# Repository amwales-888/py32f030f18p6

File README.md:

# py32f030f18p6
Simple breakout board for py32f030f18p6

- 3.3v LDO powered from 5V USB.
- UART connectivity to USB via ch340k optionally connected using jumpers.
- ARM SWD programming interface header.
- All other pins are broken out to headers.
- 1 LED optionally connected to pin PB5 using jumper.
- 1 Button optionally connected to pin PA8 using jumper.
- 1 Button connected to RESET pin, pulled high.
- Booloader selected by putting jumper across BOOT0 and 3v3 pins

<table>
  <tr>
    <td> </td>
    <td> </td>
  </tr>
  <tr>
    <td> </td>
    <td> </td>
  </tr>
  <tr>
    <td> </td>
    <td> </td>
  </tr>
  <tr>
    <td> </td>
  </tr>
</table>

Resources

<li>https://www.puyasemi.com/en/py32_series.html</li>
<li>https://www.eevblog.com/forum/microcontrollers/$0-11-py32f002a-m0-24mhz-320kb-actually-324kb-more-peripherals/</li>
<li>https://www.cnblogs.com/milton/p/18168592</li>
<li>https://github.com/IOsetting/py32f0-template/tree/main</li>
<li>https://www.cnblogs.com/milton/p/17111286.html</li>
<li>https://www.cnblogs.com/milton/p/18168592</li>
<li>https://www.lcsc.com/product-detail/C3018715.html</li>

<BR>

Notes - Assembled board with 24Mhz crystal, flashed and tested with simple LED blink/UART code via the connected via USB. Used jlink clone connected via SWD and built with keil uvision, connected jlink to reset pin. Verified running at 48Mhz by timing blink rate of LED. Have not tested bootloader configuration yet.

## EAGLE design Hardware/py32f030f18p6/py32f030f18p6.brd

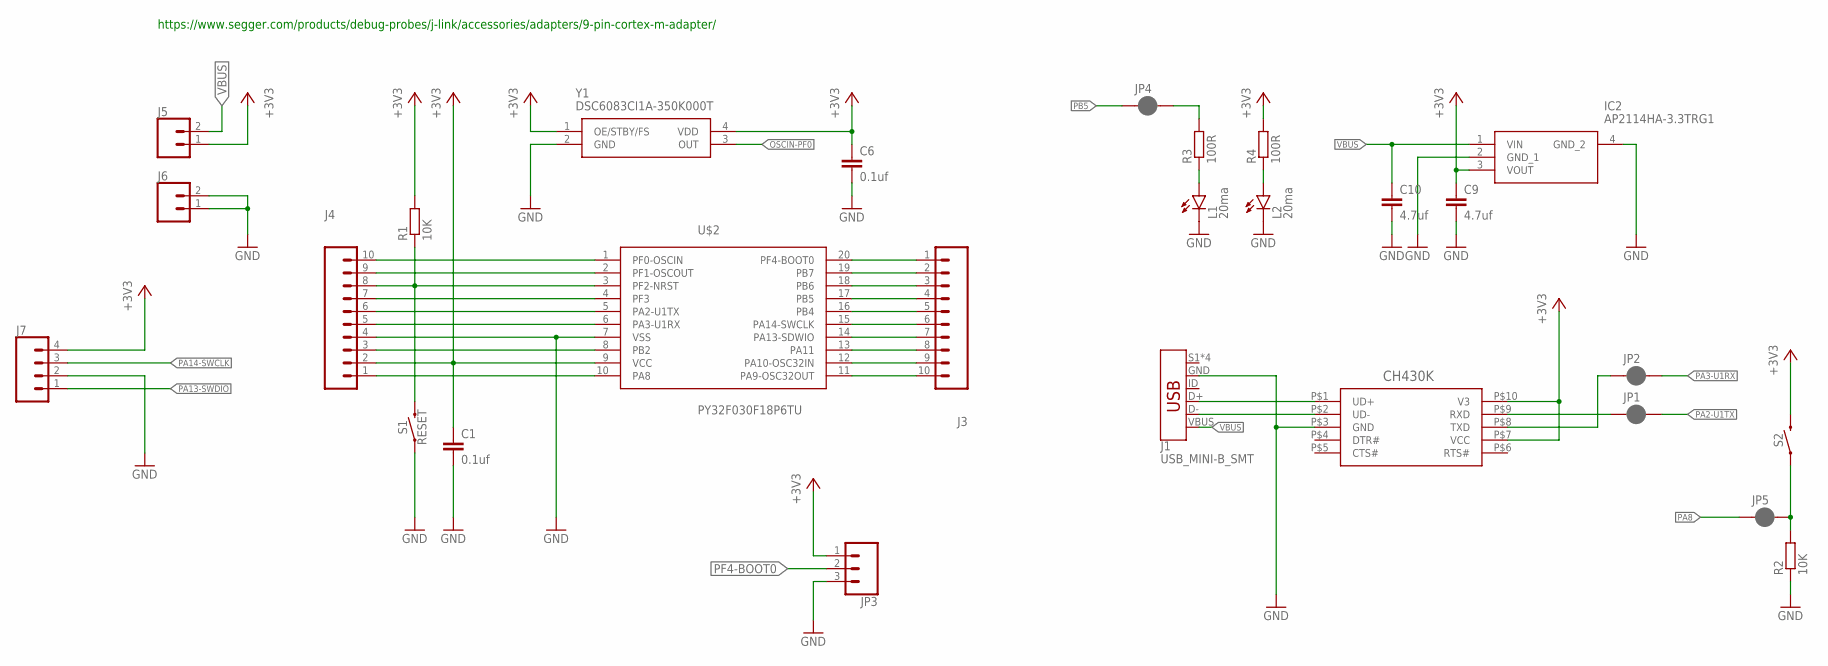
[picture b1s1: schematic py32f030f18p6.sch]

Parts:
C1, C6: 0.1uf; C0805
C9, C10: 4.7uf; C1206
IC2: AP2114HA-3.3TRG1; SOT230P700X180-4N
J1: USB_MINI-B_SMT; USB-MINIB
J3, J4: CONN_10"; 1X10
J5, J6: CONN_02; 1X02
J7: CONN_04PTH; 1X04
JP1, JP2, JP4, JP5: JUMPER-SMT_2_NC_PASTE_SILK; SMT-JUMPER_2_NC_PASTE_SILK
JP3: 455-1750-1-ND; 1X03
L1, L2: 20ma; SML0805
R1, R2: 10K; R0805
R3, R4: 100R; R0805
S1, S2: RESET; TACTILE_SWITCH_SMD_6.0X3.5MM
U$1: CH430K; ESSOP-10
U$2: PY32F030F18P6TU; TSSOP20
Y1: DSC6083CI1A-350K000T; DSC6083CI1A350K000T

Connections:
+3V3: C1.1, C6.1, C9.1, IC2.3 (VOUT), J4.2, J5.1, J7.4, JP3.1, R1.2, R4.2, S2.2, U$1.P$7 (VCC), U$1.P$10 (V3), U$2.9 (VCC), Y1.1 (OE/STBY/FS), Y1.4 (VDD)
GND: C1.2, C6.2, C9.2, C10.2, IC2.2 (GND_1), IC2.4 (GND_2), J1.GND, J4.4, J6.1, J6.2, J7.2, JP3.3, L1.C, L2.C, R2.1, S1.1, U$1.P$3 (GND), U$2.7 (VSS), Y1.2 (GND)
unnamed: L1.A, R3.1
unnamed: JP4.2, R3.2
unnamed: JP5.2, R2.2, S2.1
unnamed: L2.A, R4.1
OSCIN-PF0: J4.10, U$2.1 (PF0-OSCIN), Y1.3 (OUT)
OSCOUT-PF1: J4.9, U$2.2 (PF1-OSCOUT)
PA2-U1TX: J4.6, JP1.2, U$2.5 (PA2-U1TX)
PA3-U1RX: J4.5, JP2.2, U$2.6 (PA3-U1RX)
PA8: J4.1, JP5.1, U$2.10 (PA8)
PA9-OSC32OUT: J3.10, U$2.11 (PA9-OSC32OUT)
PA10-OSC32IN: J3.9, U$2.12 (PA10-OSC32IN)
PA11: J3.8, U$2.13 (PA11)
PA13-SWDIO: J3.7, J7.1, U$2.14 (PA13-SDWIO)
PA14-SWCLK: J3.6, J7.3, U$2.15 (PA14-SWCLK)
PB2: J4.3, U$2.8 (PB2)
PB4: J3.5, U$2.16 (PB4)
PB5: J3.4, JP4.1, U$2.17 (PB5)
PB6: J3.3, U$2.18 (PB6)
PB7: J3.2, U$2.19 (PB7)
PF2-NRST: J4.8, R1.1, S1.2, U$2.3 (PF2-NRST)
PF3: J4.7, U$2.4 (PF3)
PF4-BOOT0: J3.1, JP3.2, U$2.20 (PF4-BOOT0)
RXD: JP1.1, U$1.P$9 (RXD)
TXD: JP2.1, U$1.P$8 (TXD)
USB_N: J1.D-, U$1.P$2 (UD-)
USB_P: J1.D+, U$1.P$1 (UD+)
VBUS: C10.1, IC2.1 (VIN), J1.VBUS, J5.2

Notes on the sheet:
https://www.segger.com/products/debug-probes/j-link/accessories/adapters/9-pin-cortex-m-adapter/

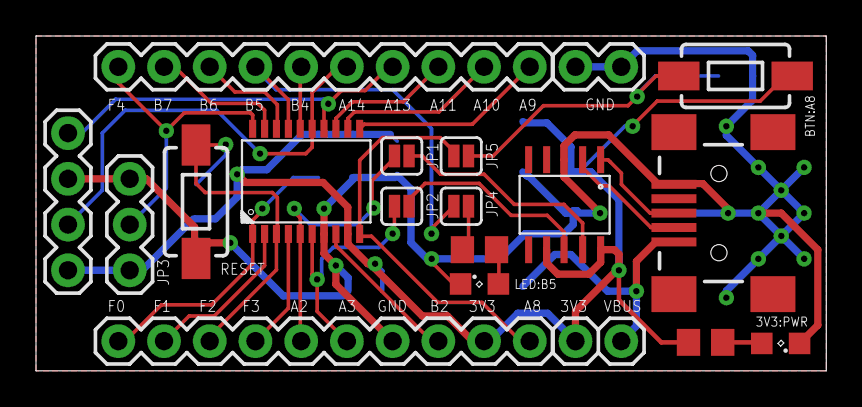
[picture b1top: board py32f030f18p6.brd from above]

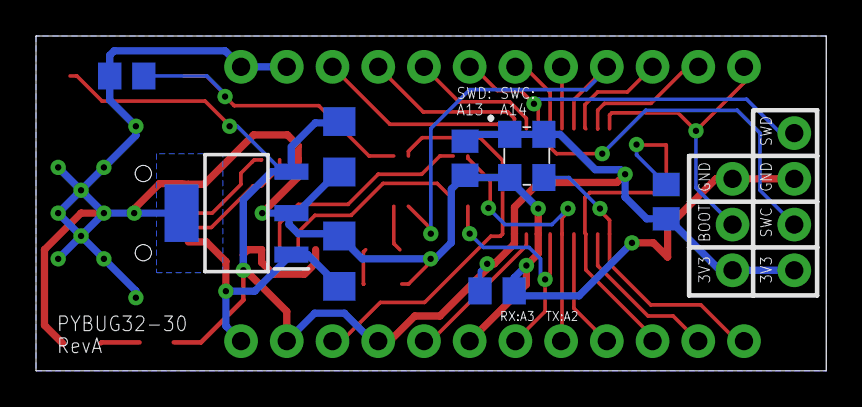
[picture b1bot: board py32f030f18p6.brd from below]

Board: 2 copper layers, 43.9 x 18.6 mm, 27 parts (8 on the bottom side), 29 nets.

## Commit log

2024-09-23 Initial checkin
2024-09-26 Remove button replace with header, removed reset pin
    Replaced the boot button with a header, removed reset pin
2024-09-27 Generate latest gerbers
2024-09-29 Added led blink firmware
    Added eaxmple led blink firmware, the resulting .hex file can be flashed to the board by plugging in the USB enabling the bootloader pins, running the PY32_IspTool connecting and downloading.
2024-10-24 blink portb pin5 thats connected to a led
2025-01-28 Added missing pullup on RX to fix bootloader issue, updated the firmware so it outputs message on uart
2025-01-28 Issue with silk screen, GND pin was labelled 3v3
2025-01-29 Added windows py32_IspTool and other documentation
2026-04-17 Reformat Directory Structure and Add KiCAD version
    Reformat Directory Structure and Add KiCAD version
2026-04-24 Deprecated old eagle layout
    Deprecated old eagle layout
2026-04-25 Update README with new resource links
    Added additional resources for the py32 series.
2026-04-25 Update README with firmware notes
    Add notes regarding firmware and board changes.
2026-04-25 Add new link to README for product detail
2026-05-21 Updated firmware, changed pad size on diode to make more hand solder friendly
    Build board and verified blink led on latest board back from jlpcb, programmed with swd using reset pin, changed pad size for diode as it was tiny.
2026-05-22 Added photos
2026-05-22 Revise notes on board assembly and testing process
    Updated notes section to reflect changes in board assembly and testing.
2026-05-22 Added 24MHz External Crystal and to run at 48MHz
2026-05-22 Revise assembly notes for board configuration
    Updated notes to reflect the addition of a 24MHz crystal and verification of 48MHz operation.

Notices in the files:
parts and their libraries:
SparkFun-Switches: Licensing: Creative Commons ShareAlike 4.0 International - https://creativecommons.org/licenses/by-sa/4.0
